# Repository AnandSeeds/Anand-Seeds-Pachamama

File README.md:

# Sistema de versionamiento AnandSeeds
## Proyecto Piloto - [SIE (Sistema de Innovación Ecológico) Cultivando Futuro!!!](http://anandseeds.co/index.php) 

Desarrollamos e implementamos soluciones TI relacionadas con IoT (Internet of Things), Big Data y Cloud Computing dirigidas al sector agropecuario y agroindustrial. Anand Seeds le permite crear una red de monitoreo integral de los parámetros agroclimáticos para alertar eventos y garantizar mejores cosechas. En nuestro equipo, entendemos que los problemas de cada productor son distintos y es por eso que trabajamos en entregar un set de información integral para el desarrollo del cultivo.

## Hardware Top

## Hardware Bottom

### INFORMACIÓN DE CONTACTO DESARROLLADORES ###

* Desarrollador: Jorge Ulises Useche Cuellar  
Est.Ingeniería Electónica de la Udistrital FJC  
E-mail: naturalmentejorge@gmail.com  
Movil: 3114813719    
Facebook: Jorge Ulises    
Twitter: @juusechec    

* Desarrollador: Diego Javier Mena Amado   
Est. Ingeniería Electrónica de la UDistrital FJC   
E-mail: ingelectronicadj@gmail.com  
Movil: 3133067541   
Facebook: Diego Javier Brown  
Twitter: @ DiegoJavierMena

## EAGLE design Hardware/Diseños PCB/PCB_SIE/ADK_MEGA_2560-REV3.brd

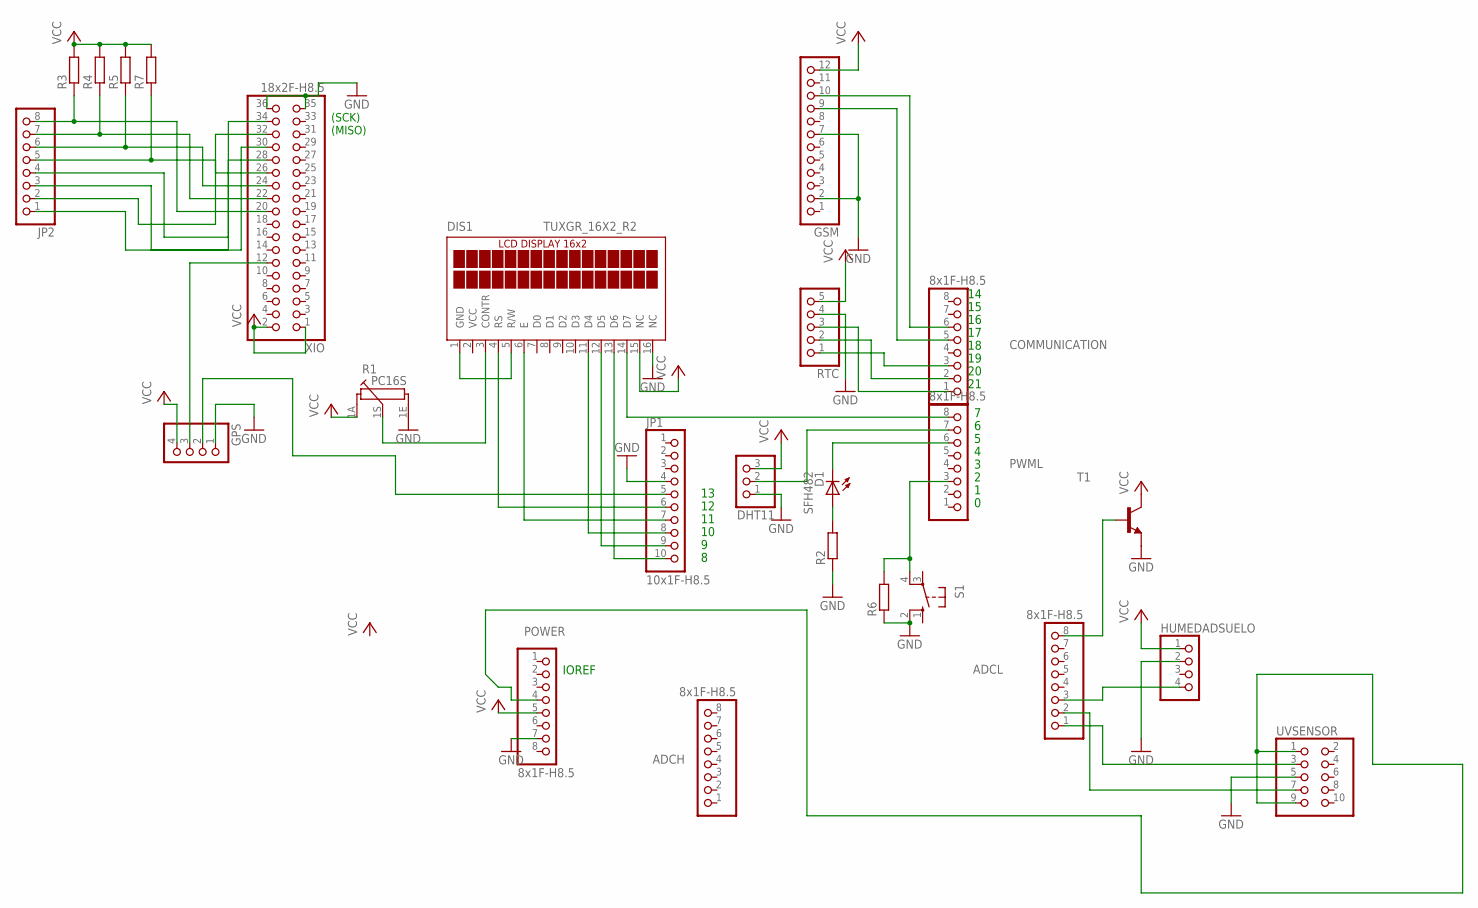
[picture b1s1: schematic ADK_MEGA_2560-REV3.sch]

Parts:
ADCH: 8x1F-H8.5; 1X08
ADCL: 8x1F-H8.5; 1X08
COMMUNICATION: 8x1F-H8.5; 1X08
D1: SFH482
DHT11: PINHD-1X3; 1X03
DIS1: TUXGR_16X2_R2
GPS: PINHD-1X4; 1X04
GSM: PINHD-1X12; 1X12
HUMEDADSUELO: PINHD-1X4; 1X04
JP1: 10x1F-H8.5; 1X10
JP2: PINHD-1X8/90; 1X08/90
POWER: 8x1F-H8.5; 1X08
PWML: 8x1F-H8.5; 1X08
R1: PC16S
R2, R3, R4, R5, R6, R7: R0204/7; 0204/7
RTC: PINHD-1X5; 1X05
S1: 10-XX; B3F-10XX
T1: 2N2222-NPN-TO92-EBC; TO92-EBC
UVSENSOR: PINHD-2X5; 2X05
XIO: 18x2F-H8.5; 2X18

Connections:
GND: DHT11.1, DIS1.16 (NC), GPS.1, GSM.2, GSM.7, HUMEDADSUELO.2, JP1.4, POWER.7, R1.1E, R2.1, R6.1, RTC.4, S1.2 (S1), T1.E, UVSENSOR.5, XIO.35, XIO.36
unnamed: DIS1.3 (CONTR), R1.1S
unnamed: D1.K (C), PWML.6
unnamed: D1.A, R2.2
unnamed: DIS1.14 (D7), PWML.8
unnamed: DIS1.1 (GND), DIS1.5 (R/W)
unnamed: DIS1.13 (D6), JP1.10
unnamed: DIS1.12 (D5), JP1.9
unnamed: DIS1.11 (D4), JP1.8
unnamed: DIS1.6 (E), JP1.7
unnamed: DIS1.4 (RS), JP1.6
unnamed: GPS.2, JP1.5
unnamed: DHT11.2, PWML.7
unnamed: GPS.3, XIO.12
unnamed: COMMUNICATION.1, RTC.3
unnamed: COMMUNICATION.2, RTC.2
unnamed: COMMUNICATION.3, RTC.1
unnamed: ADCL.3, HUMEDADSUELO.4
unnamed: ADCL.8, T1.B
unnamed: ADCL.2, UVSENSOR.7
unnamed: ADCL.1, UVSENSOR.3
unnamed: PWML.3, R6.2, S1.4 (P1)
unnamed: COMMUNICATION.6, GSM.10
unnamed: COMMUNICATION.5, GSM.9
unnamed 24: JP2.8, R3.1, XIO.20; also elsewhere on the board
unnamed 25: JP2.7, R4.1, XIO.22; also elsewhere on the board
unnamed 26: JP2.6, R5.1, XIO.24; also elsewhere on the board
unnamed 27: JP2.5, R7.1, XIO.26; also elsewhere on the board
unnamed 28: JP2.4, XIO.28; also elsewhere on the board
unnamed 29: JP2.3, XIO.30; also elsewhere on the board
unnamed 30: JP2.2, XIO.32; also elsewhere on the board
unnamed 31: JP2.1, XIO.34; also elsewhere on the board

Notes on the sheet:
(SCK)
(MISO)
IOREF

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
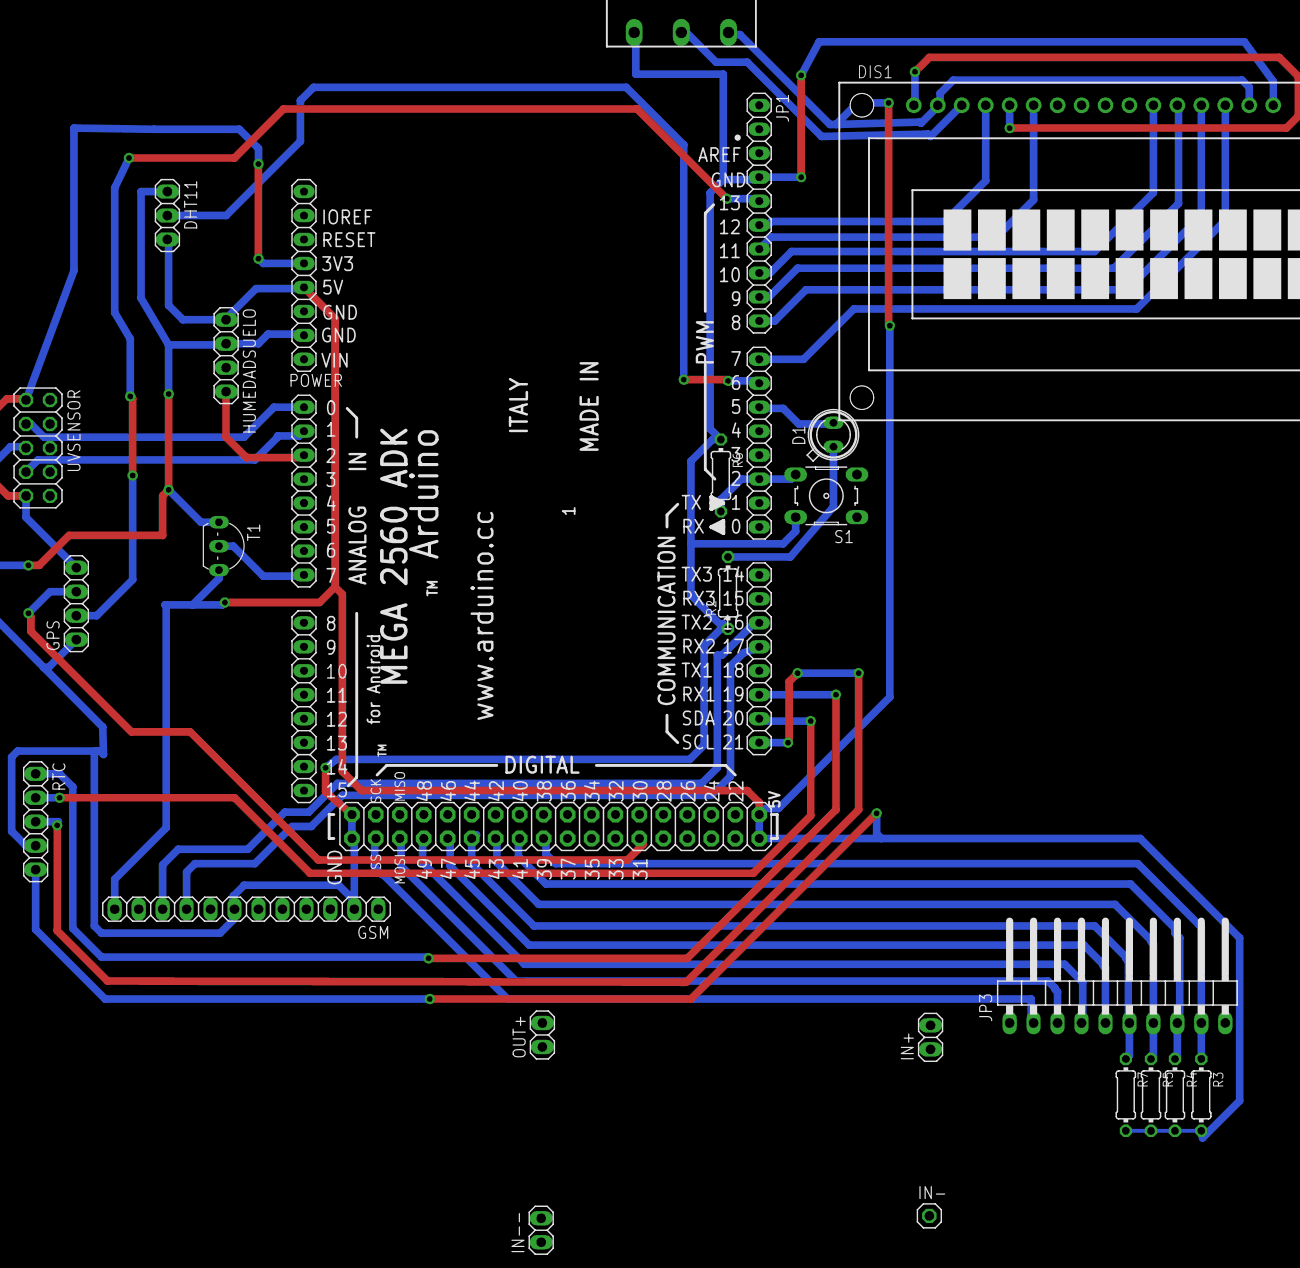
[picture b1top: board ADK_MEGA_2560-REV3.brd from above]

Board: 2 copper layers, 29 parts (0 on the bottom side), 34 nets.

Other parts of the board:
IN+: 1X02
IN-: 1X01
IN--: 1X02
JP3: 1X10/90
OUT+: 1X02

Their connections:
unnamed 24: JP3.9; also elsewhere on the board
unnamed 25: JP3.8; also elsewhere on the board
unnamed 26: JP3.7; also elsewhere on the board
unnamed 27: JP3.6; also elsewhere on the board
unnamed 28: JP3.5; also elsewhere on the board
unnamed 29: JP3.4; also elsewhere on the board
unnamed 30: JP3.3; also elsewhere on the board
unnamed 31: JP3.2; also elsewhere on the board

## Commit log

2016-02-27 Se añaden carpetas para alojar versionamiento de la hack-actividad
2016-02-27 Se añaden carpetas para versionamiento de hardware y web informativa
2016-02-27 Se complementan datasheets de componentes electricos y electronicos
2016-02-27 Agregando la parte de SARA
2016-02-27 Se agregan los bloques de componentes gráficos
2016-02-27 Correcci[on en el inicio de sesión y estilos
2016-02-27 Se agrega código fuente compilando de lectura de sensores
2016-02-27 Se documenta un poco más el código, hay que mejorar la forma en como se explican los métodos.
2016-02-27 Se agrega formato al código con eclipse.
2016-02-27 Se cambia extensión para que pueda ser leido por arduino
2016-02-27 Se construye una carpeta indispensable para arduino
2016-02-27 Se crean los módulos de registro de usuario y de emplazamiento
2016-02-27 Se añade esquema de conexiones, archivo disponible para Fritzing
2016-02-27 Se agrega servicio web para probar conectividad por GSM
2016-02-27 Se corrigen errores sobre el web service
2016-02-27 Se añaden librerias
2016-02-27 Se sube backup de sitio web para presentación
2016-02-27 Transmisión de datos funcionando
2016-02-27 Correcciones al servicio web
2016-02-27 Se añade arreglo de floats en matriz de caracteres para concatenar el envio de datos
2016-02-28 Se modifica arreglo para remover espacios y se vinculan variables dinamicas
2016-02-28 Se modifica la página de inicio
2016-02-28 Modificación a la página de registro de usuarios
2016-02-28 Se corrige el registro de datos y la consulta
2016-02-28 Se agrega la página de visor de mapas para la ubicación de los dispositivos
2016-02-28 Se añade funcionalidad de acceso a datos por teclado con variables dinamicas
2016-03-06 Últimos cambios
2016-03-13 Se sube arquitectura del Servidordonde se aloja SARA
2016-03-13 Se añaden paquetes de conexiones electricas hechas en Fritzing
2016-03-23 Se hacen arreglos de funcionalidades registro emplazamiento y usuario
2016-03-23 Se suben modificaciones del formulario de acceso y se comprimen librerias del microcontrolador
2016-03-23 Se agrega código organizado
2016-03-24 Se mejora la legibilidad del código fuente
2016-03-24 Se agrega código de prueba del módulo GPS
2016-03-24 Se sube codigo fuente organizado
2016-03-25 Código funcional y bonito
2016-03-26 Se añade codigo para seleccionar opciones con el teclado matricial y se sobre-escriben archivos compilados y en funcionamiento
2016-04-01 Se suben archivos de diseño PCB
2016-04-27 se añade esquematicos, diseño PCB y archivos gerber para impresion
2016-04-27 Se modifica la posicion del GPS, se corrijen paths y se distancian sensores
2016-05-27 Se arreglan los puntos de geolocalización
2016-05-28 Se mejora el servicio web que consulta puntos
2016-05-28 Se corrigen los warnings de la funcion degubGSM y pushSlow
2016-05-28 Se añade auto-scroll para mensajes
2016-05-29 Mensaje de selección de Operador Móvil y Selector de Configuración APN Movistar, Claro y Virgin
2016-05-29 Se reparó servicio web para las gráficas de seguimiento de variables
2016-05-29 Se invierten los parametros de latitud y longitud
2016-05-31 Se realiza autenticación segura SARA
2016-05-31 Se arregla sensado de batería
2016-06-01 Se corrige el número de intentos
2016-06-01 Se añaden comentarios a funciones adicionales
2016-06-01 Funcionando
2016-06-01 Ahora si funcionando de verdad
2016-06-01 Se quita visualización de datos GSM/GPRS transpararente
2016-06-01 No envía datos cuando el GPS no está disponible
2016-06-01 Arreglando espacios
2016-06-01 Se mejora funcion enviarDatosSim para que en el momento de obtener coordendas GPS ejecute la funcion enviarDatosSIM
2016-06-04 Se añade la carpeta de fotos para ver el crecimiento
2016-06-04 Se añade una pequeña info para el readme
    :D
2016-06-04 ajustes markdown
2016-06-05 Usando el código con atom
2016-07-25 Se añade codigo fuente para test de comandos AT
2016-07-26 Se añade archivo para la comprensión de los comandos AT empleados hasta el momento y algunos útiles para obtener las coordenadas GPS sin la ayuda del modulo gps implementado hasta el momento
2016-07-27 Se añaden ficheros para compilar el codigo del micro con ATOM y se añaden comandos AT para realizar llamadas telefonicas
2016-08-12 Se suben fotos del proyecto SIE en protoboard
2016-08-13 agregando bibliotecas
2016-08-13 se configura para que funcione con plattform-ide
2016-08-13 Se agregar operadores telefonicos de Colombia
2016-08-13 Se eliminan librerias innecesarias y se deja estable el codigo fuente
2016-08-14 Gráficos temporales funcionando SOLO HTML
2016-08-14 Traducción
